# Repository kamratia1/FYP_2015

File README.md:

# Control of a MEMS Scanning Mirror for Display Applications
Imperial College London. Electrical and Electronic Engineering. 
Final Year Project. Kishan Amratia

The repository is split into different folders: 

* __MATLAB Files__: Contains all MATLAB scripts and files for the simulation model developed for the project
* __Microcontroller Files__: Contains software for the microcontroller
* __PCB Design Files__: Contains the EAGLE PCB designs and circuit schematics
* __PICOCAP Documents and Config__: Contains the software, documents and configuration files for the PICOCAP capacitance sensor chip
* __Video__: Contains slow motion video capture of the mirror (400fps)

Additional information on how to use these files is provided in the appendix of the final report

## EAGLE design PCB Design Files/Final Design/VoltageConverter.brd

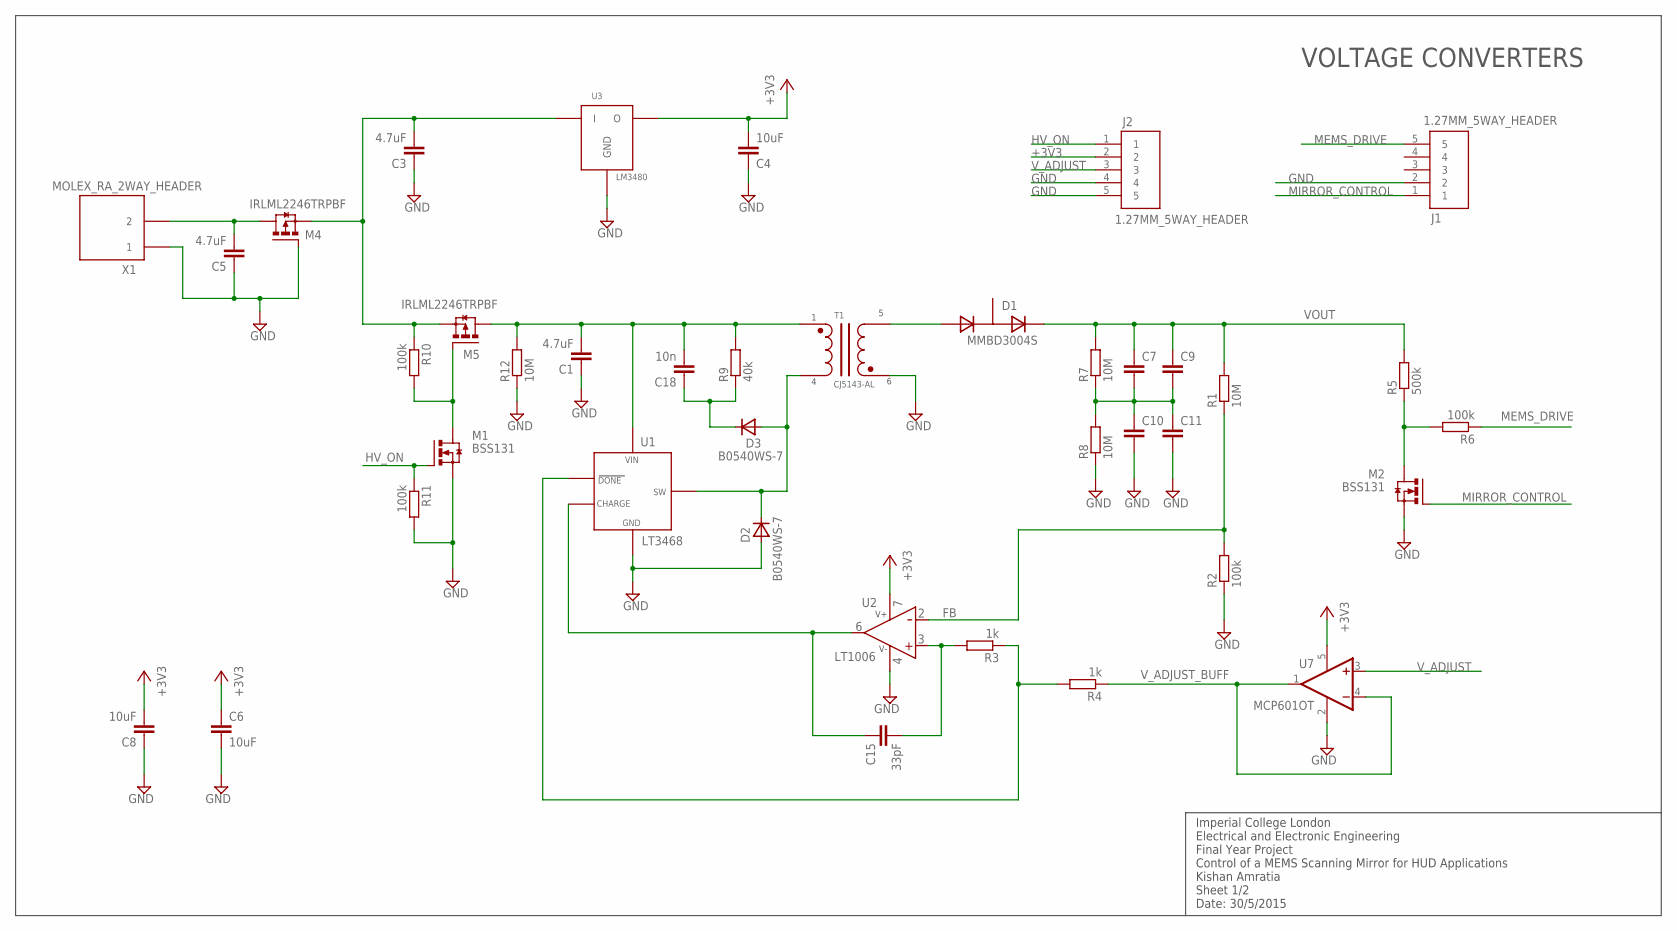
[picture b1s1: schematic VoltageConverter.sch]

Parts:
C1, C3, C5: 4.7uF; C0603K
C4, C6, C8: 10uF; C0603
C7, C9, C10, C11: C-EUC2220K; C2220K
C15: 33pF; C0603
C18: 10n; C0603K
D1: MMBD3004S; SOT-23
D2, D3: B0540WS-7; SOD-323
J1, J2: 1.27MM_5WAY_HEADER
M1, M2: BSS131; SOT-23
M4, M5: IRLML2246TRPBF; SOT-23
R1, R7, R8, R12: 10M; R0603
R2, R6, R10, R11: 100k; R0603
R3, R4: 1k; R0603
R5: 500k; R0603
R9: 40k; R0603
T1: CJ5143-AL; CJ45143-AL
U1: LT3468; TSOT-23
U2: LT1006; SOIC127P600X175-8N
U3: LM3480; SOT-23
U7: MCP601OT; SOT23-5
X1: MOLEX_RA_2WAY_HEADER

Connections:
+3V3: C4.2, C6.1, C8.2, J2.2, U2.7, U3.A (O), U7.5 (V+)
CHARGE: C15.1, U1.4, U2.6
DONE: R3.1, R4.2, U1.3
FB: R1.1, R2.2, U2.2
GND: C1.1, C3.1, C4.1, C5.1, C6.2, C8.1, C10.2, C11.2, D2.A, J1.2, J2.4, J2.5, M1.K (S), M2.K (S), M4.A (G), R2.1, R8.1, R11.2, R12.1, T1.5, U1.2, U2.4, U3.K1A2 (GND), U7.2 (V-), X1.P$1 (1)
HV_ON: J2.1, M1.A (G), R11.1
MEMS_DRIVE: J1.5, R6.1
MIRROR_CONTROL: J1.1, M2.A (G)
unnamed: C7.2, C9.2, C10.1, C11.1, R7.1, R8.2
unnamed: D1.A, T1.6
unnamed: C15.2, R3.2, U2.3
unnamed: M2.K1A2 (D), R5.1, R6.2
unnamed: M1.K1A2 (D), M5.A (G), R10.2
unnamed: C18.1, D3.K, R9.1
SW: D2.K, D3.A, T1.4, U1.1
VIN_LT3468: C1.2, C18.2, M5.K1A2 (D), R9.2, R12.2, T1.1, U1.5
VOUT: C7.1, C9.1, D1.K, R1.2, R5.2, R7.2
V_ADJUST: J2.3, U7.3 (+IN)
V_ADJUST_BUFF: R4.1, U7.1 (OUT), U7.4 (-IN)
V_IN: C5.2, M4.K1A2 (D), X1.P$2 (2)
V_IN2: C3.2, M4.K (S), M5.K (S), R10.1, U3.K (I)

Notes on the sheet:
Imperial College London Electrical and Electronic Engineering Final Year Project Control of a MEMS Scanning Mirror for HUD Applications Kishan Amratia Sheet 1/2 Date: 30/5/2015
VOLTAGE CONVERTERS

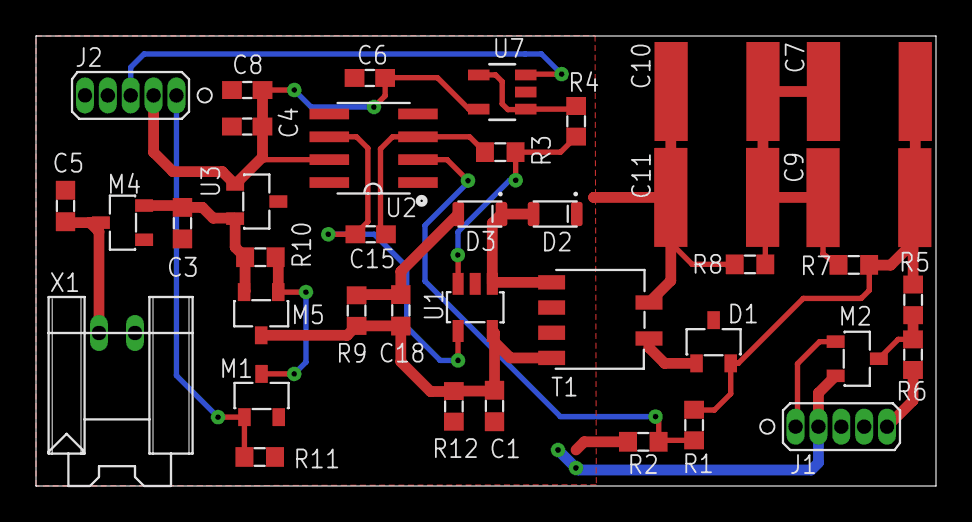
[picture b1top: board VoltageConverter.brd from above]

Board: 2 copper layers, 50.0 x 25.0 mm, 39 parts (0 on the bottom side), 21 nets.

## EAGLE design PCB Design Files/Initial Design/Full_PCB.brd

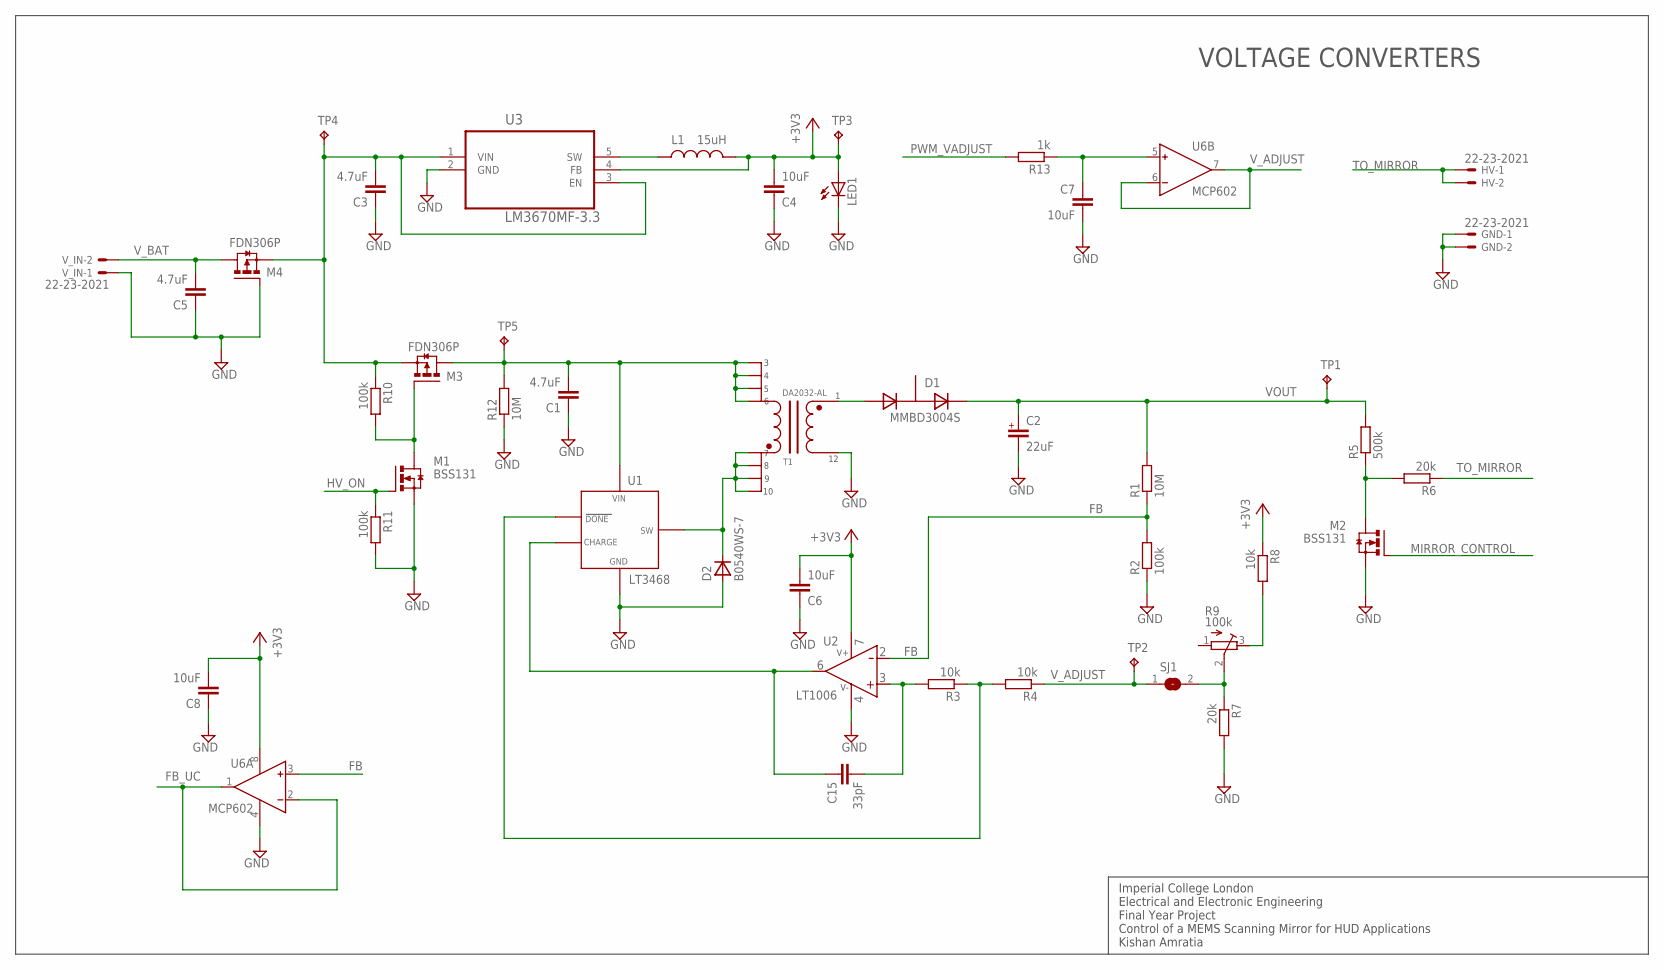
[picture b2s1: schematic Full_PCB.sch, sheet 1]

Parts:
C1, C3, C5: 4.7uF; C0603K
C2: 22uF; 5MM-RADIAL-LEAD
C4, C6, C7, C8: 10uF; C0603
C15: 33pF; C0603
D1: MMBD3004S; SOT-23
D2: B0540WS-7; SOD-323
GND: 22-23-2021
HV: 22-23-2021
L1: 15uH; IFSC1515AHER150M01
LED1: LEDCHIPLED_0603; CHIPLED_0603
M1, M2: BSS131; SOT-23
M3, M4: FDN306P; SSOT-3
R1, R12: 10M; R0603
R2, R10, R11: 100k; R0603
R3, R4, R8: 10k; R0603
R5: 500k; R1206
R6: 20k; R1206
R7: 20k; R0603
R9: 100k; TC33X-2-104E
R13: 1k; R0603
SJ1: SJ
T1: DA2032-AL
TP1, TP2, TP3, TP4, TP5: TPB1,27; B1,27
U1: LT3468; TSOT-23
U2: LT1006; SOIC127P600X175-8N
U3: LM3670MF-3.3; SOT95P284X122-5N
U6: MCP602; SOIC127P600X175-8N
V_IN: 22-23-2021

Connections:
+3V3: C4.2, C6.2, C8.2, L1.2, LED1.A, R8.1, TP3.TP, U2.7, U3.4 (FB), U6.8 (V+); also elsewhere on the board
FB: R1.1, R2.2, U2.2, U6.3 (IN+)
FB_UC: U6.1 (OUT), U6.2 (IN-); also elsewhere on the board
GND: C1.1, C2.2, C3.1, C4.1, C5.1, C6.1, C7.2, C8.1, D2.A, GND.1, GND.2, LED1.C, M1.K (S), M2.K (S), M4.1 (G), R2.1, R7.2, R11.2, R12.1, T1.12, U1.2, U2.4, U3.2 (GND), U6.4 (V-), V_IN.1; also elsewhere on the board
HV_ON: M1.A (G), R11.1; also elsewhere on the board
MIRROR_CONTROL: M2.A (G); also elsewhere on the board
unnamed: C7.1, R13.1, U6.5 (IN+)
unnamed: C15.1, U1.4, U2.6
unnamed: D1.A, T1.1
unnamed: R8.2, R9.3
unnamed: C1.2, M3.3 (D), R12.2, T1.3, T1.4, T1.5, T1.6, TP5.TP, U1.5
unnamed: R3.1, R4.2, U1.3
unnamed: C15.2, R3.2, U2.3
unnamed: M2.K1A2 (D), R5.1, R6.2
unnamed: R7.1, R9.2, SJ1.2
unnamed: D2.K, T1.7, T1.8, T1.9, T1.10, U1.1
unnamed: M1.K1A2 (D), M3.1 (G), R10.2
unnamed: L1.1, U3.5 (SW)
PWM_VADJUST: R13.2; also elsewhere on the board
TO_MIRROR: HV.1, HV.2, R6.1
VOUT: C2.1+, D1.K, R1.2, R5.2, TP1.TP
V_ADJUST: R4.1, SJ1.1, TP2.TP, U6.6 (IN-), U6.7 (OUT)
V_BAT: C5.2, M4.3 (D), V_IN.2
V_IN: C3.2, M3.2 (S), M4.2 (S), R10.1, TP4.TP, U3.1 (VIN), U3.3 (EN)

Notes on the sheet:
Imperial College London Electrical and Electronic Engineering Final Year Project Control of a MEMS Scanning Mirror for HUD Applications Kishan Amratia
VOLTAGE CONVERTERS

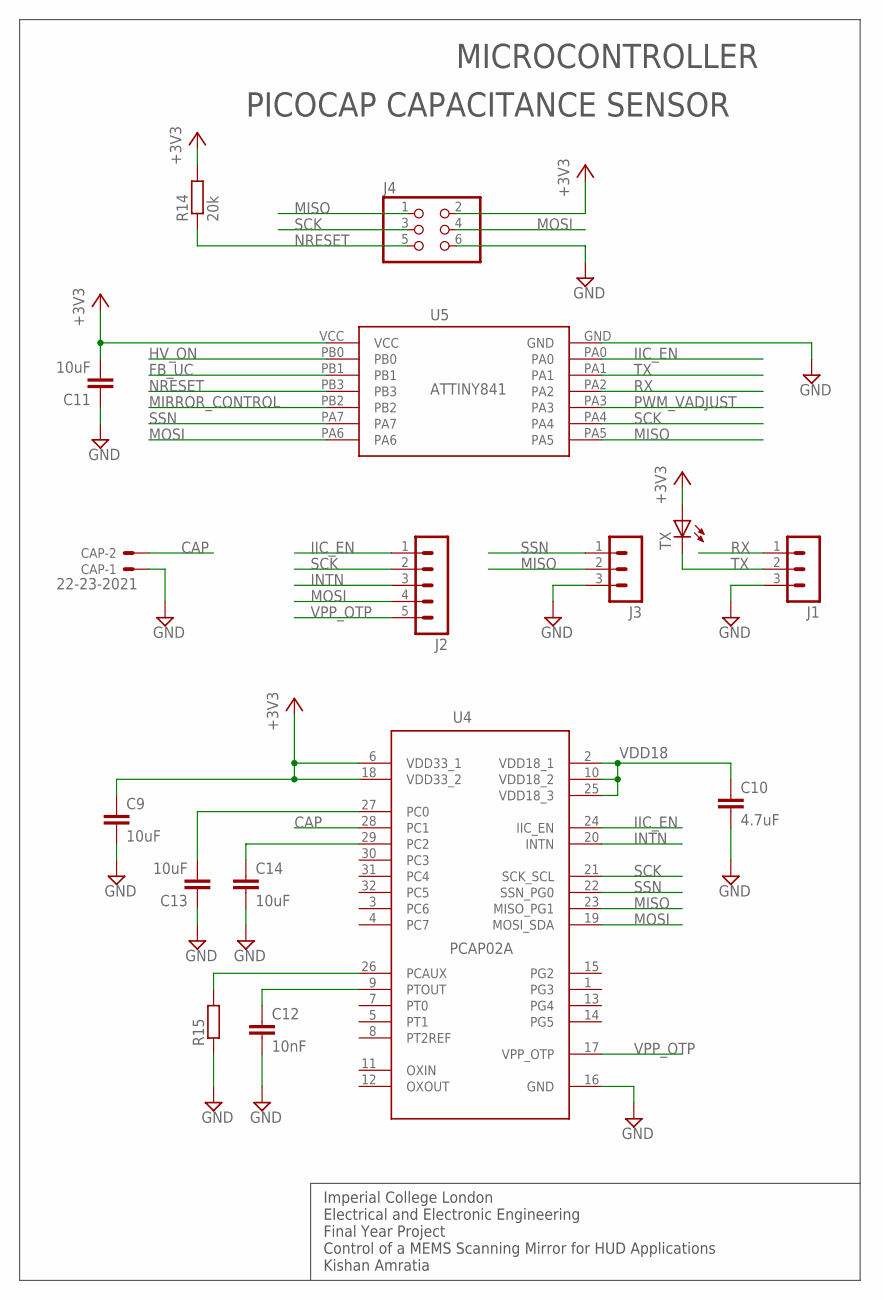
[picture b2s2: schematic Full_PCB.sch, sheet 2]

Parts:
C9, C11, C13, C14: 10uF; C0603K
C10: 4.7uF; C0603K
C12: 10nF; C0603K
CAP: 22-23-2021
J1, J3: MA03-1
J2: MA05-1
J4: PINHD-2X3; 2X03
R14: 20k; R0603
R15: R-EU_R0603; R0603
TX: LEDCHIPLED_0603; CHIPLED_0603
U4: PCAP02A; QFN32
U5: ATTINY841; SOIC-14

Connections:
+3V3: C9.1, C11.2, J4.2, R14.2, TX.A, U4.6 (VDD33_1), U4.18 (VDD33_2), U5.VCC; also elsewhere on the board
CAP: CAP.2, U4.28 (PC1)
FB_UC: U5.PB1; also elsewhere on the board
GND: C9.2, C10.2, C11.1, C12.2, C13.1, C14.2, CAP.1, J1.3, J3.3, J4.6, R15.1, U4.16 (GND), U5.GND; also elsewhere on the board
HV_ON: U5.PB0; also elsewhere on the board
IIC_EN: J2.1, U4.24 (IIC_EN), U5.PA0
INTN: J2.3, U4.20 (INTN)
MIRROR_CONTROL: U5.PB2; also elsewhere on the board
MISO: J3.2, J4.1, U4.23 (MISO_PG1), U5.PA5
MOSI: J2.4, J4.4, U4.19 (MOSI_SDA), U5.PA6
unnamed: C12.1, U4.9 (PTOUT)
unnamed: R15.2, U4.26 (PCAUX)
unnamed: C13.2, U4.27 (PC0)
unnamed: C14.1, U4.29 (PC2)
NRESET: J4.5, R14.1, U5.PB3
PWM_VADJUST: U5.PA3; also elsewhere on the board
RX: J1.1, U5.PA2
SCK: J2.2, J4.3, U4.21 (SCK_SCL), U5.PA4
SSN: J3.1, U4.22 (SSN_PG0), U5.PA7
TX: J1.2, TX.C, U5.PA1
VDD18: C10.1, U4.2 (VDD18_1), U4.10 (VDD18_2), U4.25 (VDD18_3)
VPP_OTP: J2.5, U4.17 (VPP_OTP)

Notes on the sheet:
Imperial College London Electrical and Electronic Engineering Final Year Project Control of a MEMS Scanning Mirror for HUD Applications Kishan Amratia
PICOCAP CAPACITANCE SENSOR
MICROCONTROLLER

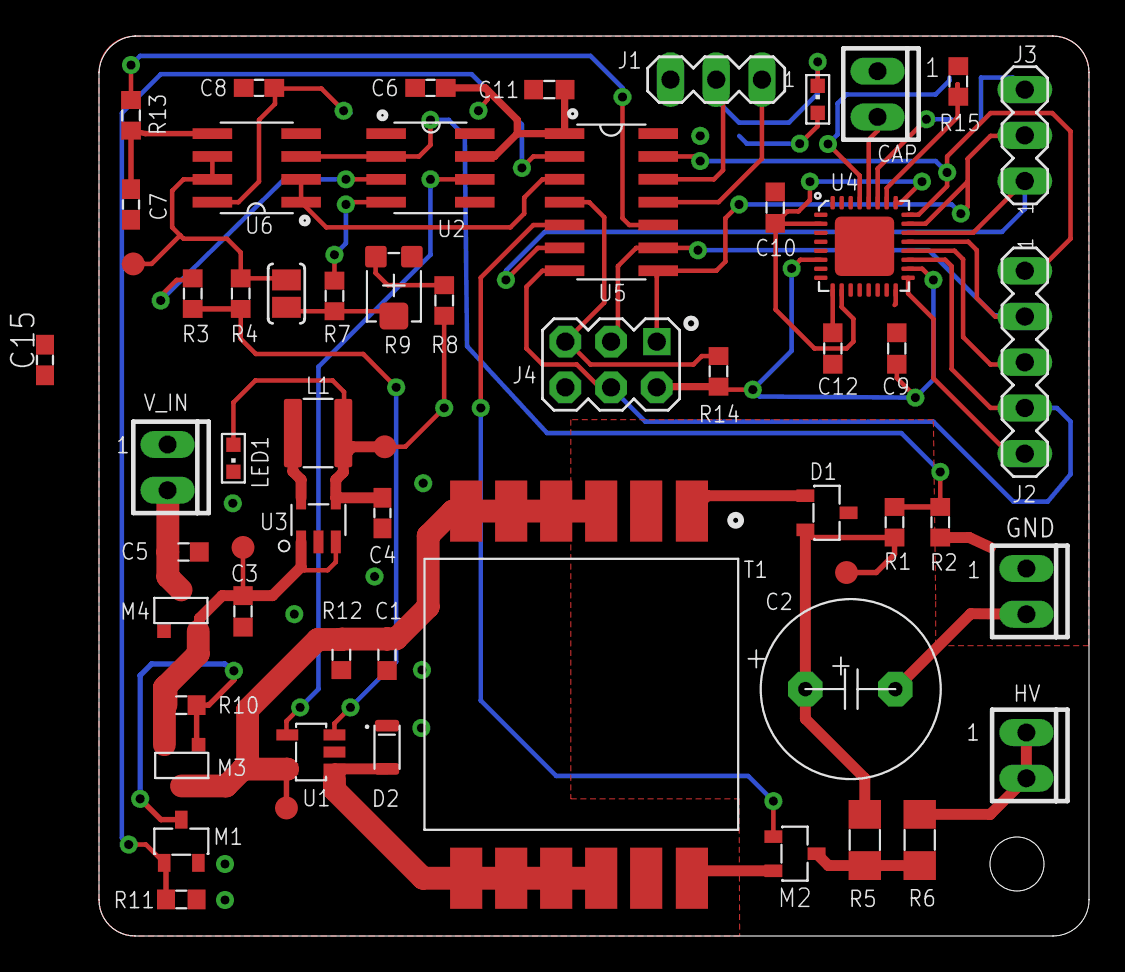
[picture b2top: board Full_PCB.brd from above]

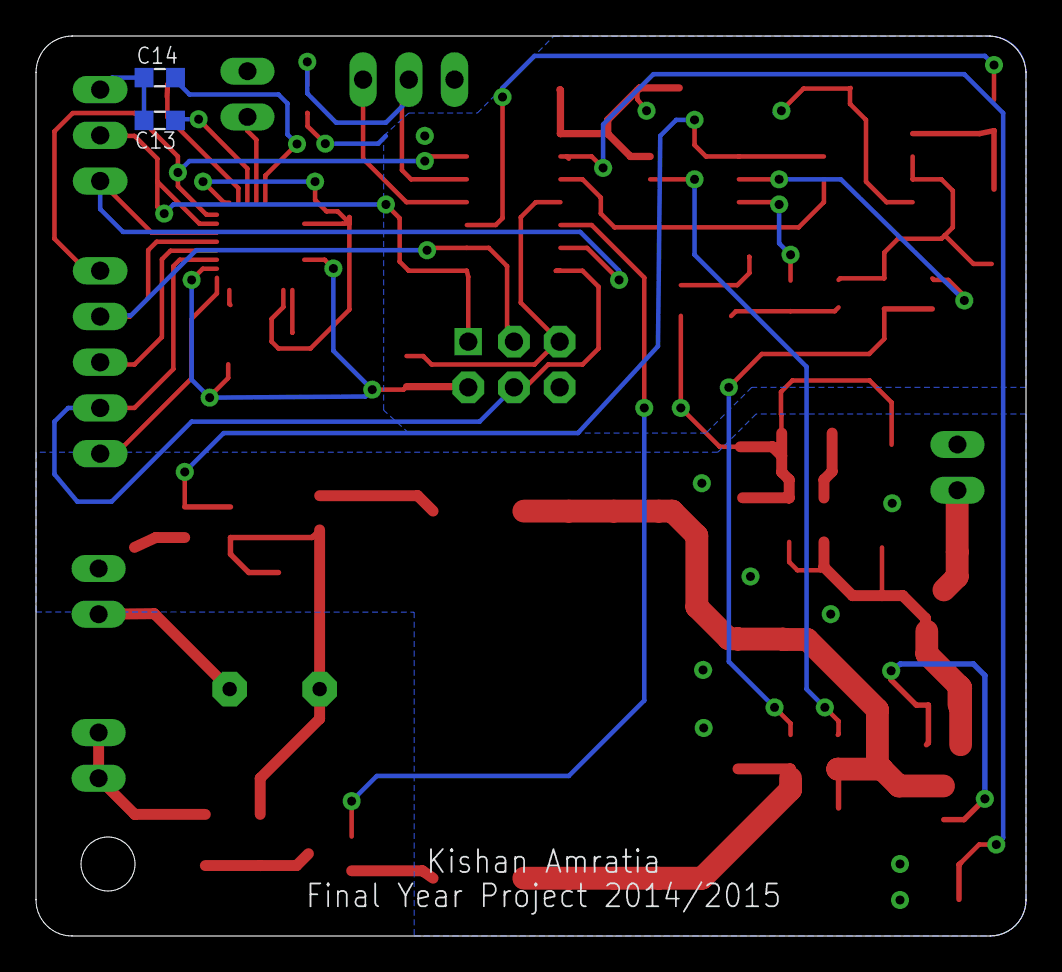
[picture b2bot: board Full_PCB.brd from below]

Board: 2 copper layers, 55.0 x 50.0 mm, 60 parts (2 on the bottom side), 40 nets.

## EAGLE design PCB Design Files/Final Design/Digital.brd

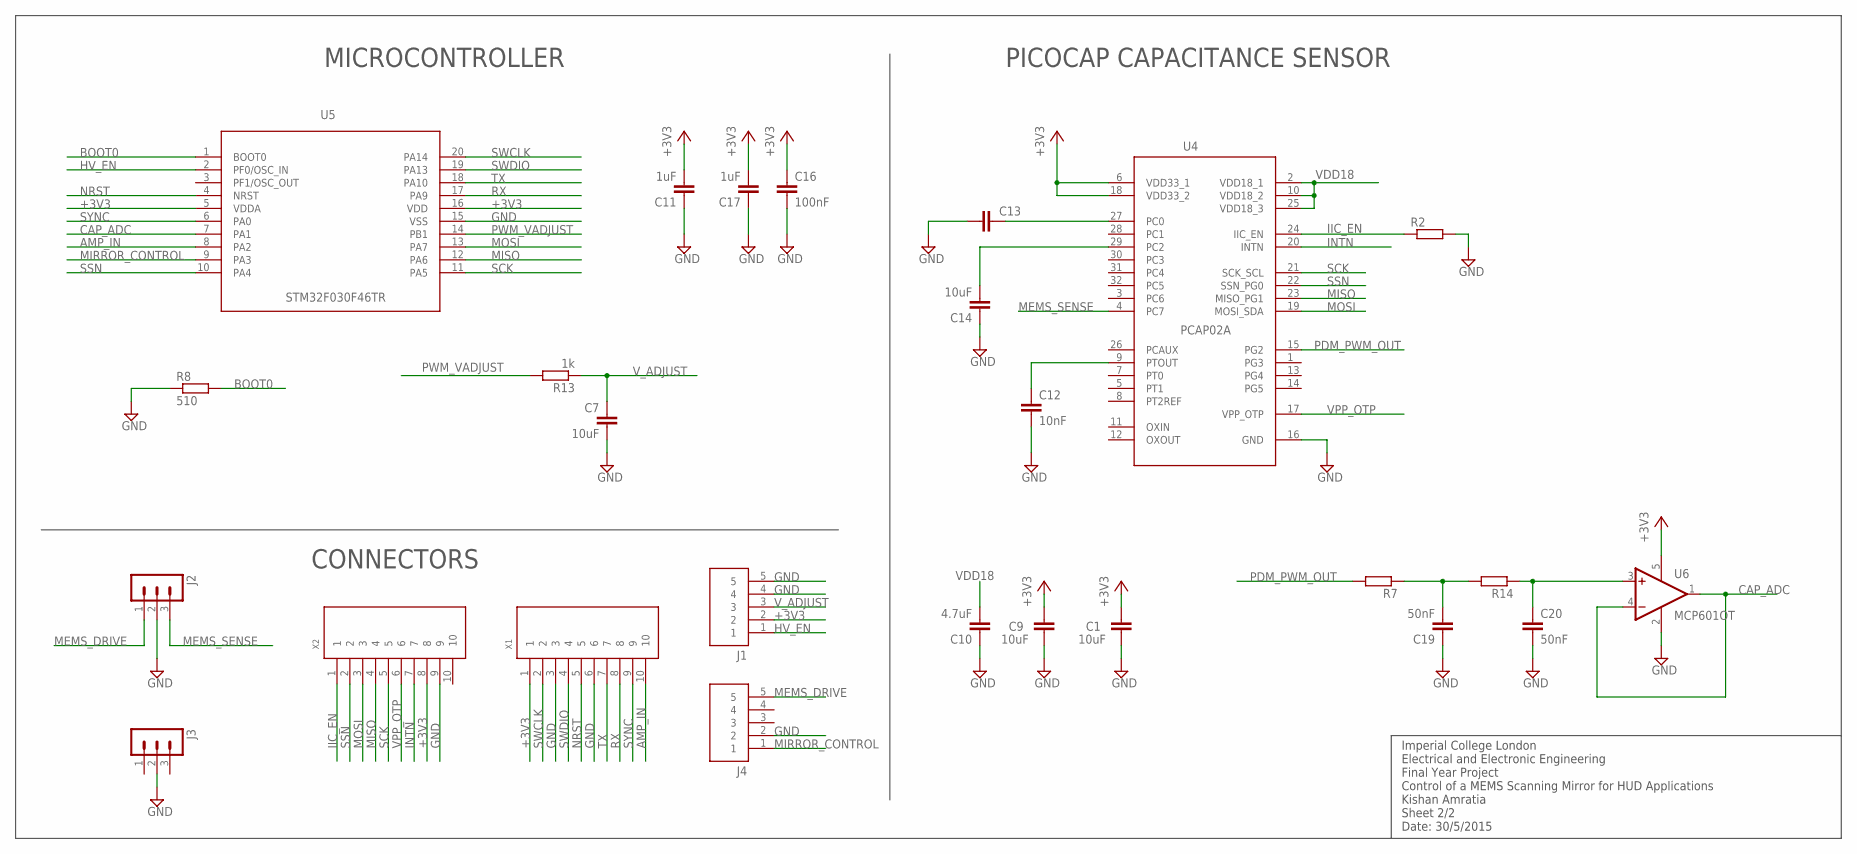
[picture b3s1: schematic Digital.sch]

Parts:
C1, C9, C14: 10uF; C0603K
C7: 10uF; C0603
C10: 4.7uF; C0603K
C11, C17: 1uF; C0603K
C12: 10nF; C0603K
C13: C-EUC0603K; C0603K
C16: 100nF; C0603K
C19, C20: 50nF; C0603K
J1, J4: 1.27MM_5WAY_HEADER
J2, J3: MA03-1
R2, R7, R14: R-EU_R0603; R0603
R8: 510; R0603
R13: 1k; R0603
U4: PCAP02A; QFN32
U5: STM32F030XX; TSOP20
U6: MCP601OT; SOT23-5
X1, X2: OMRON_FPC_0.5MM_10WAY

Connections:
+3V3: C1.1, C9.1, C11.2, C16.1, C17.2, J1.2, U4.6 (VDD33_1), U4.18 (VDD33_2), U5.5 (VDDA), U5.16 (VDD), U6.5 (V+), X1.1, X2.8
AMP_IN: U5.8 (PA2), X1.10
BOOT0: R8.2, U5.1 (BOOT0)
CAP_ADC: U5.7 (PA1), U6.1 (OUT), U6.4 (-IN)
GND: C1.2, C7.2, C9.2, C10.1, C11.1, C12.2, C13.1, C14.1, C16.2, C17.1, C19.1, C20.2, J1.4, J1.5, J2.2, J3.2, J4.2, R2.2, R8.1, U4.16 (GND), U5.15 (VSS), U6.2 (V-), X1.3, X1.6, X2.9
HV_EN: J1.1, U5.2 (PF0/OSC_IN)
IIC_EN: R2.1, U4.24 (IIC_EN), X2.1
INTN: U4.20 (INTN), X2.7
MEMS_DRIVE: J2.1, J4.5
MEMS_SENSE: J2.3, U4.4 (PC7)
MIRROR_CONTROL: J4.1, U5.9 (PA3)
MISO: U4.23 (MISO_PG1), U5.12 (PA6), X2.4
MOSI: U4.19 (MOSI_SDA), U5.13 (PA7), X2.3
unnamed: C19.2, R7.1, R14.2
unnamed: C12.1, U4.9 (PTOUT)
unnamed: C13.2, U4.27 (PC0)
unnamed: C14.2, U4.29 (PC2)
NRST: U5.4 (NRST), X1.5
PDM: C20.1, R14.1, U6.3 (+IN)
PDM_PWM_OUT: R7.2, U4.15 (PG2)
PWM_VADJUST: R13.2, U5.14 (PB1)
RX: U5.17 (PA9), X1.8
SCK: U4.21 (SCK_SCL), U5.11 (PA5), X2.5
SSN: U4.22 (SSN_PG0), U5.10 (PA4), X2.2
SWCLK: U5.20 (PA14), X1.2
SWDIO: U5.19 (PA13), X1.4
SYNC: U5.6 (PA0), X1.9
TX: U5.18 (PA10), X1.7
VDD18: C10.2, U4.2 (VDD18_1), U4.10 (VDD18_2), U4.25 (VDD18_3)
VPP_OTP: U4.17 (VPP_OTP), X2.6
V_ADJUST: C7.1, J1.3, R13.1

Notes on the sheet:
Imperial College London Electrical and Electronic Engineering Final Year Project Control of a MEMS Scanning Mirror for HUD Applications Kishan Amratia Sheet 2/2 Date: 30/5/2015
PICOCAP CAPACITANCE SENSOR
MICROCONTROLLER
CONNECTORS

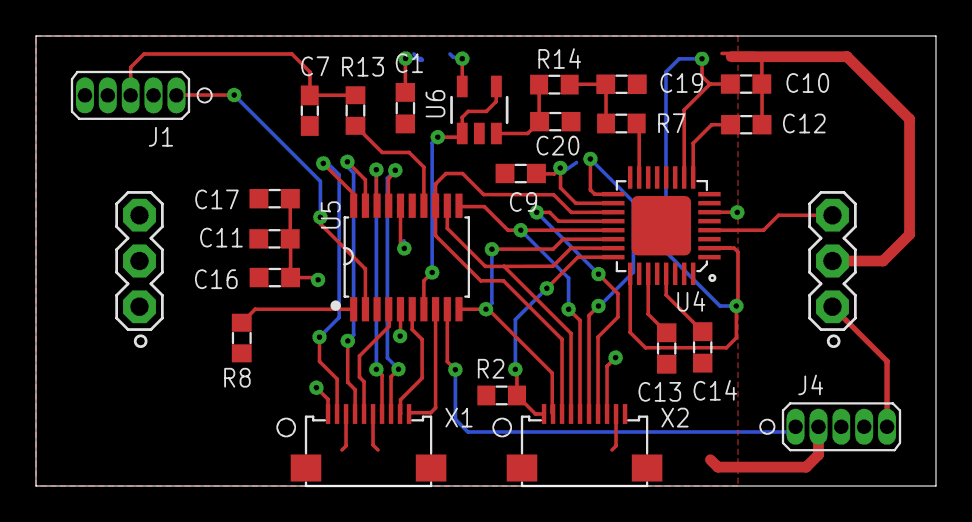
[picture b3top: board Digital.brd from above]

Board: 2 copper layers, 50.0 x 25.0 mm, 26 parts (0 on the bottom side), 31 nets.

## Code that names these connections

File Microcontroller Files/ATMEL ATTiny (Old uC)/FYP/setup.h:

//#define CLOCK8MHZ		// define this if system frequency is set at 8MHz

#ifdef CLOCK8MHZ
#define F_CPU		8000000UL 
#else
#define F_CPU		1000000UL
#endif

#define PCAP_FREQ	200000

#define HV_LIMIT	160
#define VCC			3.3

// pin definitions
#define HV_ON							PB0
#define HV_ON_PORT						PORTB
#define HV_ON_DIRECTION_PORT			DDRB

#define MIRROR_CONTROL					PB2			//PB1
#define	MIRROR_CONTROL_PORT				PORTB
#define MIRROR_CONTROL_DIRECTION_PORT	DDRB

#define PWM_ADJUST						PA3			
#define	PWM_ADJUST_PORT					PORTA		
#define PWM_DIRECTION_PORT				DDRA		
#define PWM_COMPARE_REGISTER			OCR0B

#define PWM_OUTPUT_COMPARE				TOCC2OE		// on the new one it is TOCC7OE

#define SYNC							PA0
#define SYNC_PORT						PORTA
#define SYNC_DIRECTION_PORT				DDRA

#define PCAP_PIN						PA7			//PB2
#define PCAP_PORT						PORTA
#define PCAP_DIRECTION_PORT				DDRA
#define PCAP_ICP						ICES1
//#define PCAP_PCINT						PCINT7

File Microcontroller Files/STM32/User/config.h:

#ifndef __config_h
#define __config_h

#include "stm32f0xx.h"
#include <RTL.h>
#include <stdio.h>

// Value definitions
#define HV_DEFAULT	50			// default value for High Voltage Converter
#define HV_LIMIT		160			// HV Converter Voltage limit
#define VCC					3.3			// Define VCC for determining the duty cycle for the HV Converter reference apprioprately

#define SAMP_FREQ		10000		// Define Sampling Frequency for the control algorithm

/* Pin Definitions */

// GPIOs
#define MIRROR_CONTROL_PIN			GPIO_Pin_8		// PC8	// In the final PCB this is PA3
#define MIRROR_CONTROL_PORT			GPIOC
#define MIRROR_CONTROL_CLK			RCC_AHBPeriph_GPIOC

#define HV_EN_PIN								GPIO_Pin_9		// PC9	// In the final PCB this is PF0
#define HV_EN_PORT							GPIOC
#define HV_EN_CLK								RCC_AHBPeriph_GPIOC

#define SYNC_PIN								GPIO_Pin_0		// PA0
#define SYNC_PORT								GPIOA
#define SYNC_CLK								RCC_AHBPeriph_GPIOA

// ADC for PICOCAP Capacitance Analogue Values
#define PCAP_PDM_PIN							GPIO_Pin_1		// PA1 
#define PCAP_PDM_PORT							GPIOA
#define PCAP_PDM_CLK							RCC_AHBPeriph_GPIOA
#define PCAP_ADC_SAMPLING_TIME		ADC_SampleTime_1_5Cycles
#define PCAP_PDM_ADC_CHANNEL			ADC_Channel_1 	

// PWM for HV Converter Voltage Adjust Definitions
#define PWM_VADJUST_PIN					GPIO_Pin_8		//PA8			// In the final PCB, this is PB1 on TIM1 Channel 3
#define PWM_VADJUST_PORT				GPIOA
#define PWM_VADJUST_CLK					RCC_AHBPeriph_GPIOA
#define PWM_VADJUST_AF_PIN			GPIO_PinSource8		
#define PWM_VADJUST_AF					GPIO_AF_2					
#define PWM_TIMER_CLK						RCC_APB2Periph_TIM1		
#define PWM_TIMER								TIM1							

// UART pin definitions can be found in serial.h

//#define DEBUG	// Defines TRACE level

#ifdef DEBUG
	#define USE_FULL_ASSERT
	#warning "Using Debug mode, for production do not use debug mode"
	#define TRACE_LEVEL TRACE_LEVEL_DEBUG
#else
	#define TRACE_LEVEL TRACE_LEVEL_INFO
#endif

#include "trace.h"

#endif

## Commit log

2015-06-18 Folder Structure and readme edit
2015-06-18 Added PCB Design Files
2015-06-18 Added ATMEL Code and Python Code
2015-06-18 Added STM32 Code
2015-06-18 Added MATLAB Files
2015-06-18 Added PICOCAP Files
2015-06-18 Added info to readme
2015-06-18 Cleaned up Ma
2015-06-18 Added config and firmware files for PICOCAP
2015-06-19 Cleaning up uC code and edited config file for PCAP
2015-06-19 Edited Config File
2015-06-19 Cleaned up uC code
2015-06-19 Added Sync signal code
2015-06-19 Added Some extra Comments for pin config
2015-12-23 Adding slow motion video captures
